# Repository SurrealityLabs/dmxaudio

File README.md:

# dmxaudio
Audio player driven by DMX512

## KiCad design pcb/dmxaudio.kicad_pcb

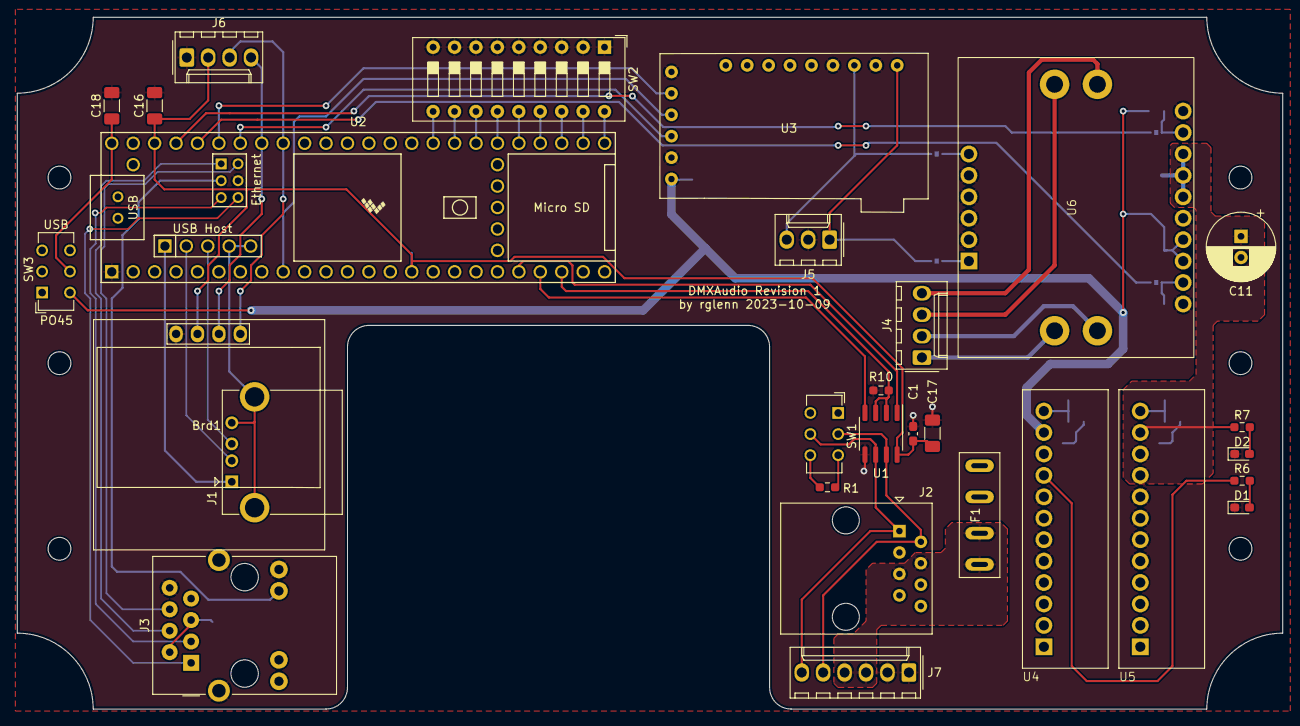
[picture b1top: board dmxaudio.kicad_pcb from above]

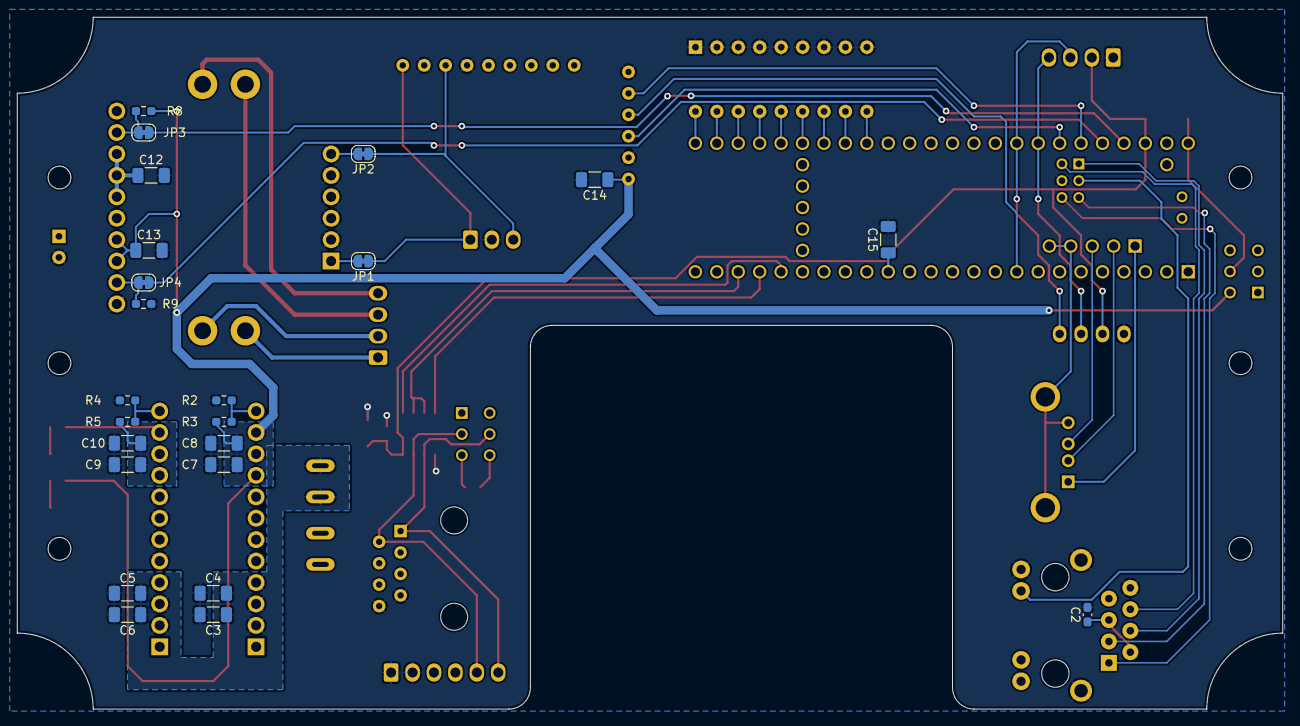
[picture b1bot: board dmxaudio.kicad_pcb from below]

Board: 2 copper layers, 150.0 x 82.0 mm, 52 parts (23 on the bottom side), 54 nets.

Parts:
Brd1: SSD1306; 128x64OLED
C1, C2: 100n; C_0603_1608Metric_Pad1.08x0.95mm_HandSolder
C3, C6: 10u; C_1206_3216Metric_Pad1.33x1.80mm_HandSolder
C4, C5, C8, C10: DNP; C_1206_3216Metric_Pad1.33x1.80mm_HandSolder
C7, C9: 22u; C_1206_3216Metric_Pad1.33x1.80mm_HandSolder
C11: 470u DNP; CP_Radial_D8.0mm_P2.50mm
C12, C13, C14, C15: 22u DNP; C_1206_3216Metric_Pad1.33x1.80mm_HandSolder
C16, C17, C18: 10u DNP; C_1206_3216Metric_Pad1.33x1.80mm_HandSolder
D1, D2: LED; LED_0603_1608Metric_Pad1.05x0.95mm_HandSolder
F1: Fuse; XF-506P
J1: USB_A; USB_A_CONNFLY_DS1095-WNR0
J2: RJ45; RJ45_Amphenol_54602-x08_Horizontal
J3: RJ45_Bel_SI-60062-F
J4, J6: Conn_01x04; Molex_KK-254_AE-6410-04A_1x04_P2.54mm_Vertical
J5: Conn_01x03; Molex_KK-254_AE-6410-03A_1x03_P2.54mm_Vertical
J7: Conn_01x06; Molex_KK-254_AE-6410-06A_1x06_P2.54mm_Vertical
JP1, JP2, JP3, JP4: SolderJumper_2_Bridged; SolderJumper-2_P1.3mm_Bridged_RoundedPad1.0x1.5mm
R1: 120; R_0603_1608Metric_Pad0.98x0.95mm_HandSolder
R2, R3, R4, R5, R8, R9: DNP; R_0603_1608Metric_Pad0.98x0.95mm_HandSolder
R6: 1K; R_0603_1608Metric_Pad0.98x0.95mm_HandSolder
R7: 2.7K; R_0603_1608Metric_Pad0.98x0.95mm_HandSolder
R10: 10K; R_0603_1608Metric_Pad0.98x0.95mm_HandSolder
SW1, SW3: SW_DPDT_x2; SW_CuK_JS202011CQN_DPDT_Straight
SW2: SW_DIP_x09; SW_DIP_SPSTx09_Slide_9.78x25.04mm_W7.62mm_P2.54mm
U1: SN65HVD11HD; SOIC-8_3.9x4.9mm_P1.27mm
U2: Teensy4.1; Teensy41
U3: GY-PCM5102
U4: K78L05-3AR3; K78LXX-3AR3
U5: K78L12-3AR3; K78LXX-3AR3
U6: CJMCU-8006

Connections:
+3V3: Brd1.2 (VCC), C1.1, C15.1, C16.1, C17.1, J6.2, U1.8 (VCC), U2.15 (3V3), U2.46 (3V3)
+24V: C3.1, C4.1, C5.1, C6.1, F1.2, U4.2 (VIN), U4.3 (VIN), U4.4 (VIN), U5.2 (VIN), U5.3 (VIN), U5.4 (VIN)
/24V_PREFUSE: F1.1, J2.4, J2.5, J7.3, J7.4
/Amplifier/5V: C7.1, C8.1, C13.1, C14.1, R3.1, R6.1, R8.1, SW3.4 (A), U3.6 (VIN), U4.9 (+VO), U4.10 (+VO), U4.11 (+V0), U6.13 (AVDD), U6.14 (AVDD)
/Amplifier/12V: C9.1, C10.1, C11.1, C12.1, R5.1, R7.1, U5.9 (+VO), U5.10 (+VO), U5.11 (+V0), U6.9 (AVCC), U6.10 (PVCCR), U6.11 (PVCCL)
/Amplifier/LEFT: JP1.2 (B), U6.1 (LINN)
/Amplifier/MUTE: JP4.2 (B), R9.1, U6.15 (MUTE)
/Amplifier/RIGHT: JP2.2 (B), U6.6 (RINN)
/Amplifier/SPEAKER_L+: J4.2, U6.18 (LP+)
/Amplifier/SPEAKER_L-: J4.1, U6.17 (LN-)
/Amplifier/SPEAKER_R+: J4.4, U6.20 (RP+)
/Amplifier/SPEAKER_R-: J4.3, U6.19 (RN-)
/Amplifier/~SD: JP3.2 (B), R8.2, U6.8 (~SD)
/DAC/BCLK: U2.43 (21_A7_RX5_BCLK1), U3.2 (BCK)
/DAC/DATA: U2.9 (7_RX2_OUT1A), U3.3 (DIN)
/DAC/LEFT: J5.1, JP1.1 (A), U3.15 (L)
/DAC/LRCLK: U2.42 (20_A6_TX5_LRCLK1), U3.4 (LRCLK)
/DAC/RIGHT: J5.3, JP2.1 (A), U3.13 (R)
/MCU/DMX_DATA: U1.1 (R), U2.20 (28_RX7)
/MCU/ETHERNET_LED: J3.L3 (LEDG_A), U2.61 (LED)
/MCU/ETHERNET_R+: J3.4 (RD+), U2.60 (R+)
/MCU/ETHERNET_R-: J3.6 (RD-), U2.65 (R-)
/MCU/ETHERNET_T+: J3.1 (TD+), U2.63 (T+)
/MCU/ETHERNET_T-: J3.3 (TD-), U2.62 (T-)
/MCU/MUTE: JP4.1 (A), U2.44 (22_A8_CTX1)
/MCU/RDM_DATA: U1.4 (D), U2.21 (29_TX7)
/MCU/RDM_SEND: R10.1, U1.2 (~RE), U1.3 (DE), U2.22 (30_CRX3)
/MCU/RS485_A: J2.1, J7.6, SW1.5 (B), U1.6 (A)
/MCU/RS485_B: J2.2, J7.5, SW1.2 (B), U1.7 (B)
/MCU/SCL: Brd1.3 (SCL), J6.4, U2.41 (19_A5_SCL)
/MCU/SDA: Brd1.4 (SDA), J6.3, U2.40 (18_A4_SDA)
/MCU/USB_D+: J1.3 (D+), U2.57 (D+)
/MCU/USB_D-: J1.2 (D-), U2.56 (D-)
/MCU/USB_GND: J1.4 (GND), J1.5 (Shield), U2.58 (GND), U2.59 (GND)
/MCU/USB_VBUS: J1.1 (VBUS), U2.55 (5V)
/MCU/~SD: JP3.1 (A), U2.45 (23_A9_CRX1_MCLK1)
GND: Brd1.1 (GND), C1.2, C2.2, C3.2, C4.2, C5.2, C6.2, C7.2, C8.2, C9.2, C10.2, C11.2, C12.2, C13.2, C14.2, C15.2, C16.2, C17.2, C18.2, D1.1 (K), D2.1 (K), J2.7, J2.8, J3.8 (GND), J3.L4 (LEDG_K), J3.SH (SHIELD), J5.2, J6.1, J7.1, J7.2, R2.2, R4.2, R9.2, R10.2, SW2.1, SW2.2, SW2.3, SW2.4, SW2.5, SW2.6, SW2.7, SW2.8, SW2.9, U1.5 (GND), U2.1 (GND), U2.34 (GND), U2.47 (GND), U2.64 (GND), U3.1 (SCK), U3.5 (GND), U3.12 (AGND), U3.14 (AGND), U4.5 (GND), U4.6 (GND), U4.7 (GND), U4.8 (GND), U5.5 (GND), U5.6 (GND), U5.7 (GND), U5.8 (GND), U6.2 (GND), U6.3 (LINP), U6.4 (RINP), U6.5 (GND), U6.7 (GND), U6.12 (GND), U6.16 (GND)
unnamed: D1.2 (A), R6.2
unnamed: D2.2 (A), R7.2
unnamed: C2.1, J3.2 (TCT), J3.5 (RCT)
unnamed: R1.1, SW1.3 (C)
unnamed: R1.2, SW1.6 (C)
unnamed: C18.1, SW3.5 (B), U2.48 (VIN)
unnamed: SW2.18, U2.25 (33_MCLK2)
unnamed: SW2.17, U2.26 (34_RX8)
unnamed: SW2.16, U2.27 (35_TX8)
unnamed: SW2.15, U2.28 (36_CS)
unnamed: SW2.14, U2.29 (37_CS)
unnamed: SW2.13, U2.30 (38_CS1_IN1)
unnamed: SW2.12, U2.31 (39_MISO1_OUT1A)
unnamed: SW2.11, U2.32 (40_A16)
unnamed: SW2.10, U2.33 (41_A17)
unnamed: R2.1, R3.2, U4.12 (TRIM)
unnamed: R4.1, R5.2, U5.12 (TRIM)

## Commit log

2023-09-17 Adding first PCB work
2023-09-19 Adding demo code used to test out features of Teensy 4.1
2023-09-20 Starting to clean up schematic and split into multiple sheets
2023-09-22 Adding much of the code. Commands to actually play audio not yet implemented.
2023-09-24 Updating files before SSD upgrade
2023-09-26 Updating schematic based on review from Mike
2023-10-29 Updated code to be feature-complete
2023-10-29 Adding PCB files sent off to fab
2024-09-26 Adding first test script
2024-09-26 Half of the planned tests are written
2024-09-27 Streamlining tests and fixing to include the proper number of bytes
2024-09-27 Adding more tests
2024-09-27 Adding 3 more tests
2024-09-27 Adding rest of tests, fixing test 16
2024-10-15 Updating tests to actually work
2024-10-15 Fixing bugs in DMXAudio code
